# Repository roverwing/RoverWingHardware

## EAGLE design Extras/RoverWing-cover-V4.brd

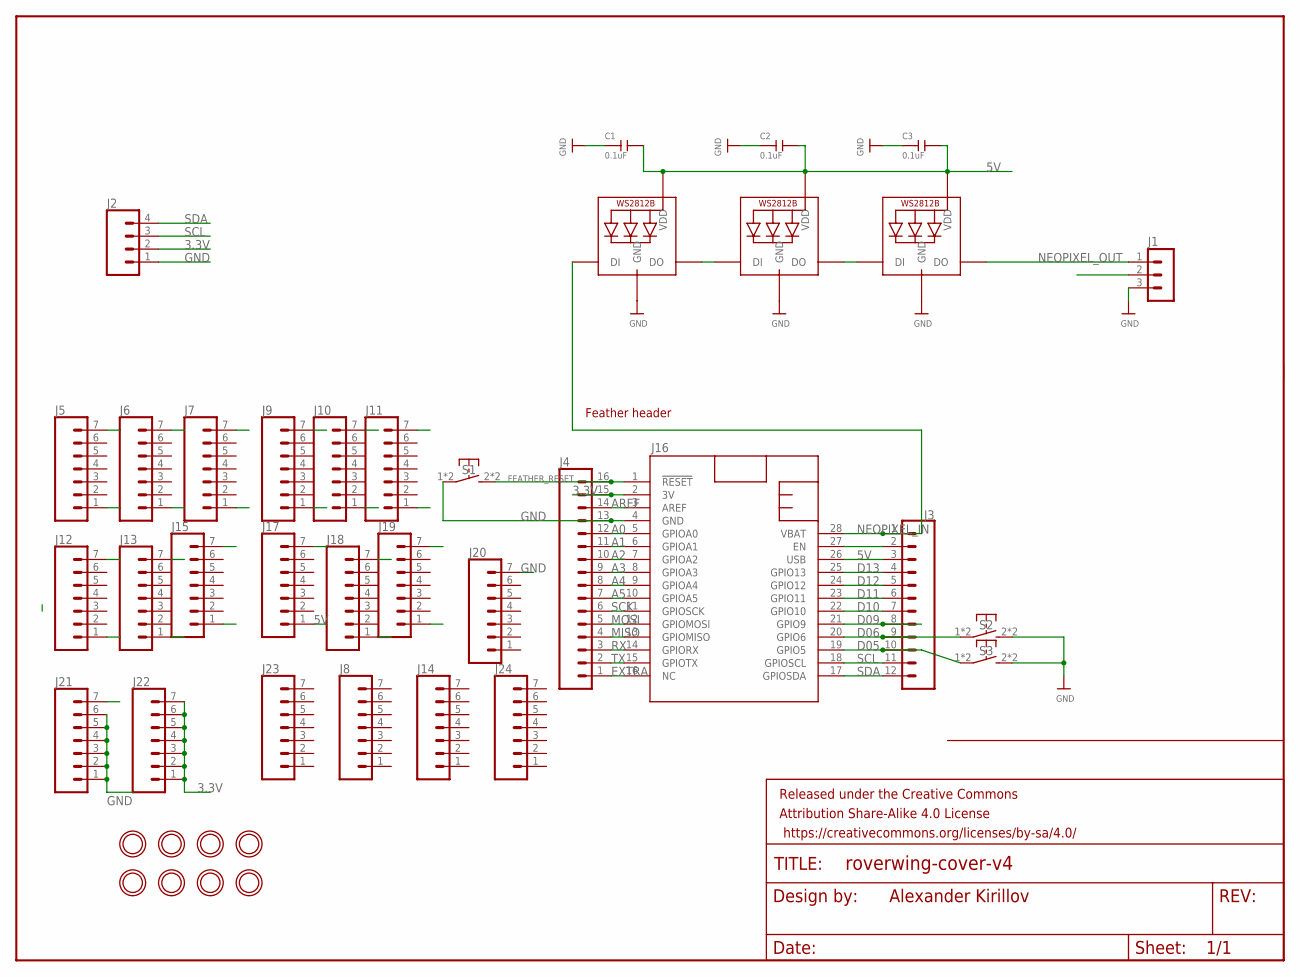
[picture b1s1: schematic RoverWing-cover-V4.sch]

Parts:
C1, C2, C3: 0.1uF; C0805
FRAME2: FRAME-LETTERNO_PACKAGE; DUMMY
J1: HEADER-PH-3P; B3B-PH-K
J2: CONN_04; 1X04
J3: CONN_12NO_SILK; 1X12_NO_SILK
J4: CONN_161X16_NO_SILK; 1X16_NO_SILK
J5, J6, J7, J8, J9, J10, J11, J12, J13, J14, J15, J17, J18, J19, J20, J21, J22, J23, J24: CONN_07NO_SILK; 1X07_NO_SILK
J16: FEATHERWING_NODIM; FEATHERWING_DIM
LED1, LED2, LED3: WS2812B5050; WS2812B
S1, S2, S3: SW-TACTILE-4.5X4.5_SMD; TL3305
U$3, U$4, U$14, U$15, U$24, U$25, U$26, U$27: MOUNTINGHOLE3.0_NPH; MOUNTINGHOLE_3.0_NPH

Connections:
3.3V: J2.2, J4.15, J16.2 (3V), J22.1, J22.2, J22.3, J22.4, J22.5, J22.6, J22.7
5V: C1.2, C2.2, C3.2, J1.2, J3.3, J16.26 (USB), J17.1, LED1.1-VDD (VDD), LED2.1-VDD (VDD), LED3.1-VDD (VDD)
A0: J4.12, J16.5 (GPIOA0), J19.7
A1: J4.11, J16.6 (GPIOA1), J18.7
A2: J4.10, J16.7 (GPIOA2), J17.7
A3: J4.9, J15.7, J16.8 (GPIOA3)
A4: J4.8, J13.7, J16.9 (GPIOA4)
A5: J4.7, J12.7, J16.10 (GPIOA5)
AREF: J4.14, J16.3 (AREF), J21.7
D05: J3.10, J7.1, J16.19 (GPIO5), S3.1, S3.4 (P1)
D06: J3.9, J9.1, J16.20 (GPIO6), S2.1, S2.4 (P1)
D09: J3.8, J10.1, J16.21 (GPIO9)
D10: J3.7, J11.1, J16.22 (GPIO10)
D11: J3.6, J12.1, J16.23 (GPIO11)
D12: J3.5, J13.1, J16.24 (GPIO12)
D13: J3.4, J15.1, J16.25 (GPIO13)
EXTRA: J4.1, J5.7, J16.16 (NC)
FEATHER_RESET: J4.16, J16.1 (!RESET), S1.2 (S1), S1.3 (S1)
GND: C1.1, C2.1, C3.1, J1.3, J2.1, J4.13, J16.4 (GND), J20.7, J21.1, J21.2, J21.3, J21.4, J21.5, J21.6, LED1.3-GND (GND), LED2.3-GND (GND), LED3.3-GND (GND), S1.1, S1.4 (P1), S2.2 (S1), S2.3 (S1), S3.2 (S1), S3.3 (S1)
MISO: J4.4, J9.7, J16.13 (GPIOMISO)
MOSI: J4.5, J10.7, J16.12 (GPIOMOSI)
unnamed: LED2.2-DOUT (DO), LED3.4-DIN (DI)
unnamed: LED1.2-DOUT (DO), LED2.4-DIN (DI)
unnamed: J3.2, J16.27 (EN), J18.1
NEOPIXEL_IN: J3.1, J16.28 (VBAT), LED1.4-DIN (DI)
NEOPIXEL_OUT: J1.1, LED3.2-DOUT (DO)
RX: J4.3, J7.7, J16.14 (GPIORX)
SCK: J4.6, J11.7, J16.11 (GPIOSCK)
SCL: J2.3, J3.11, J6.1, J16.18 (GPIOSCL)
SDA: J2.4, J3.12, J5.1, J16.17 (GPIOSDA)
TX: J4.2, J6.7, J16.15 (GPIOTX)

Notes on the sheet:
Alexander Kirillov
Feather header

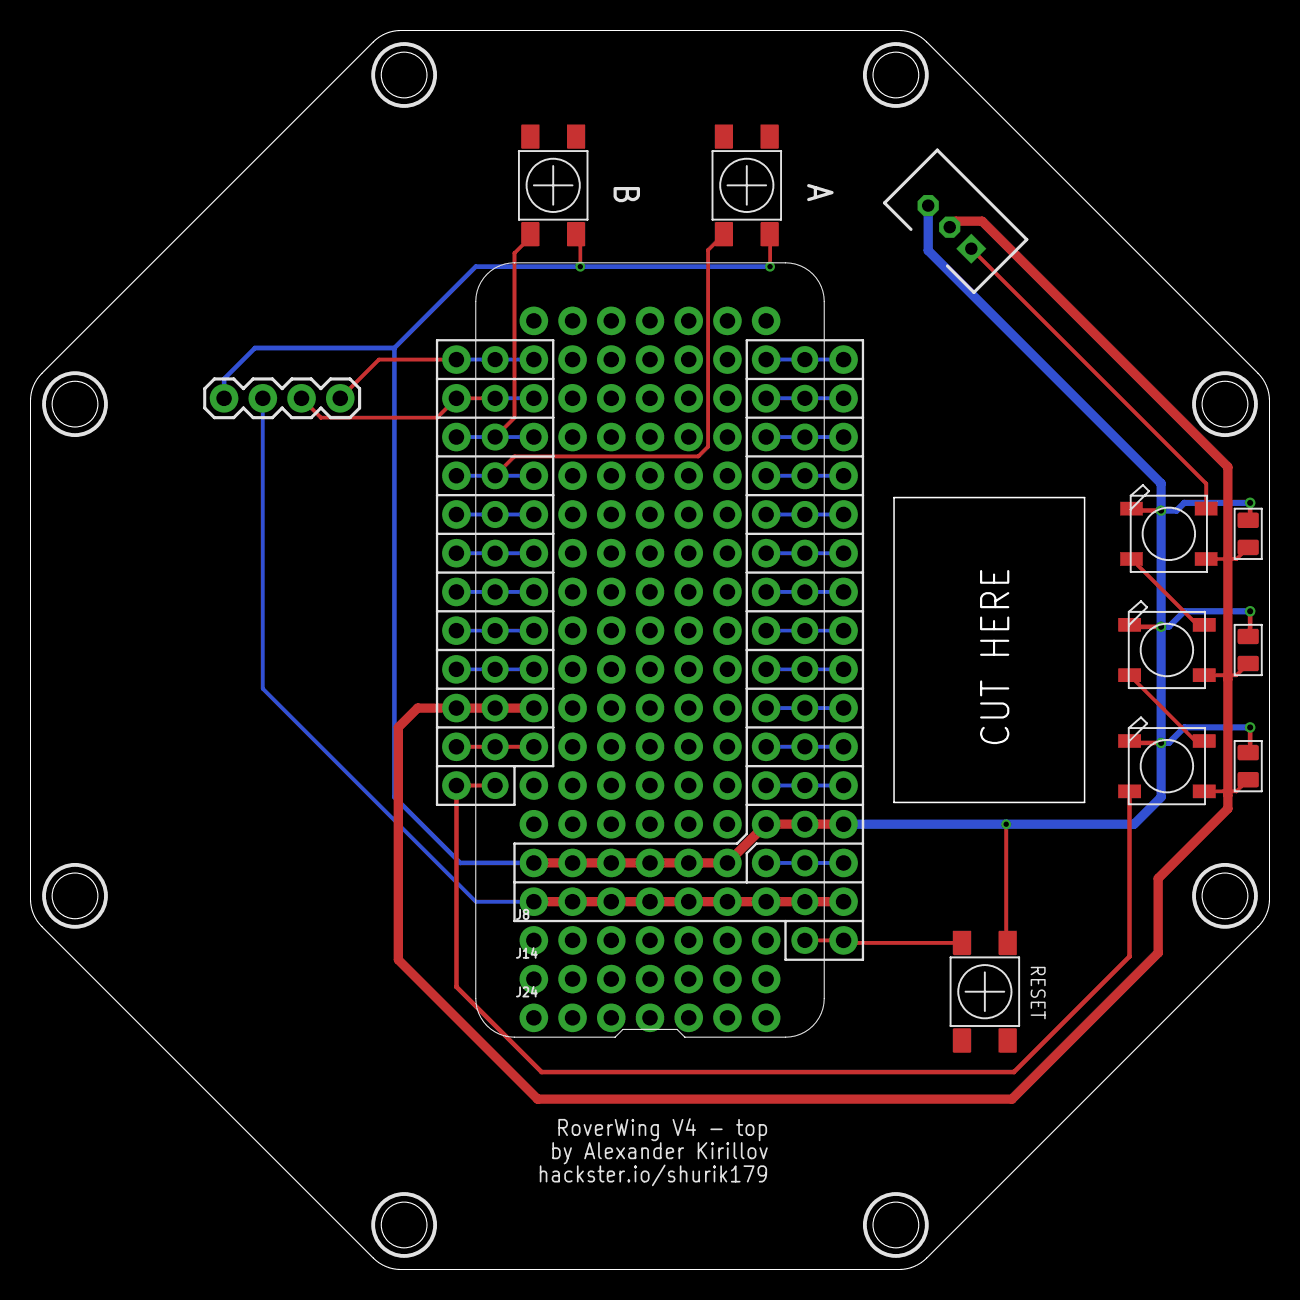
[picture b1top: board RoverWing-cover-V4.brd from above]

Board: 2 copper layers, 81.3 x 81.3 mm, 42 parts (0 on the bottom side), 31 nets.

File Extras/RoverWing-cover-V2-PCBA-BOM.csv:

Order list for /Users/davidbershadsky/Documents/Roverwing/RoverWingHardware/Extras/RoverWing-cover-V2.0.sch
Exported from EAGLE with DesignLink

Quantity	Value	Package	Order code	Manufacturer	Manuf. Code	Availability	Price (from)	Description
3	0.1uF	C0805	96Y8186	AVX	04025C104KAT2A	9540	0.131	AVX - 04025C104KAT2A - SMD Multilayer Ceramic Capacitor, 0.1 &#181;F, 50 V, 0402 [1005 Metric], &#177; 10%, X7R
1	FRAME-LETTERNO_PACKAGE	DUMMY	unknown					
1	HEADER-PH-3PSIDEENTRY	S3B-PH-K	38K8070	JST (JAPAN SOLDERLESS TERMINALS)	S3B-PH-K-S (LF)(SN)	7505	0.075	JST (JAPAN SOLDERLESS TERMINALS) - S3B-PH-K-S (LF)(SN) - Pin Header, Wire-to-Board, 2 mm, 1 Rows, 3 Contacts, Through Hole, PH Series
1		1X04	unknown					
1		1X12_NO_SILK	unknown					
1		1X16_NO_SILK	unknown					
4	HEADER-PH-6PSIDEENTRY	S6B-PH-K	unknown					
8		1X06_NO_SILK	unknown					
1	FEATHERWING_NODIM	FEATHERWING_DIM	unknown					
17		1X07_NO_SILK	unknown					
3		LED3535	77Y5297	ADAFRUIT	2659	0	49.5	ADAFRUIT - 2659 - NEOPIXEL MINI 3535 RGB LEDS W/ INTEGRATED DRIVER CHIP - WHITE - PACK OF 10
3	SW-TACTILE-4.5X4.5_SMD	TL3305	84Y2774	E-SWITCH	TL3305AF160QG	2716	0.126	E-SWITCH - TL3305AF160QG - Tactile Switch, Ultraminiature, TL3305 Series, Top Actuated, Surface Mount, Round Button, 160 gf
8	MOUNTINGHOLE3.0_NPH	MOUNTINGHOLE_3.0_NPH	unknown

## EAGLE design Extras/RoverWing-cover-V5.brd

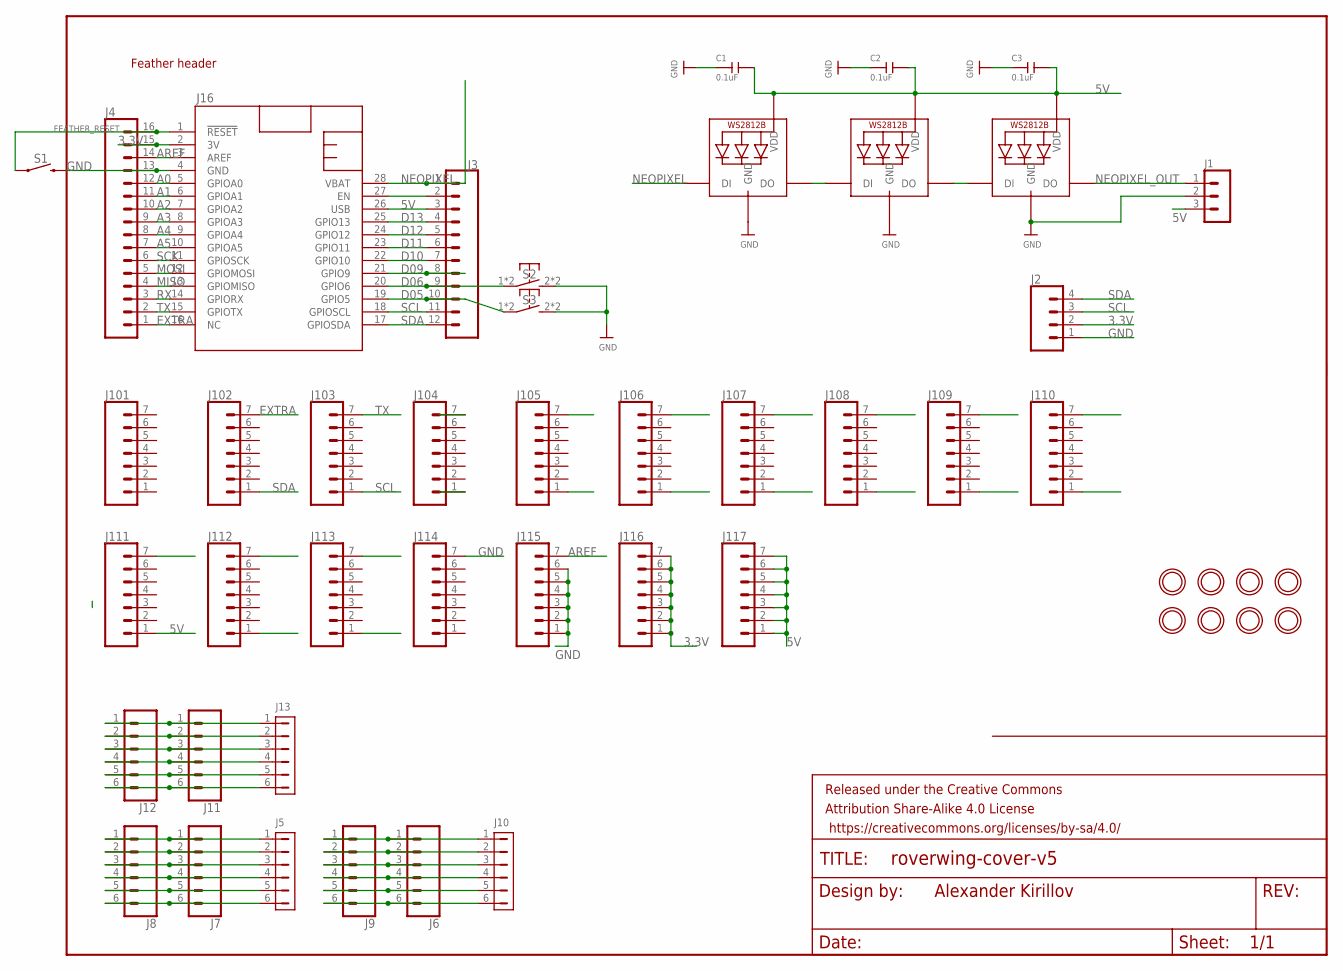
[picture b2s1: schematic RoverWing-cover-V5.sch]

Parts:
C1, C2, C3: 0.1uF; C0805
FRAME2: FRAME-LETTERNO_PACKAGE; DUMMY
J1: HEADER-PH-3PSIDEENTRY; S3B-PH-K
J2: CONN_04; 1X04
J3: CONN_12NO_SILK; 1X12_NO_SILK
J4: CONN_161X16_NO_SILK; 1X16_NO_SILK
J5, J10, J13: HEADER-PH-6PSIDEENTRY; S6B-PH-K
J6, J7, J8, J9, J11, J12: CONN_06NO_SILK_NO_POP; 1X06_NO_SILK
J16: FEATHERWING_NODIM; FEATHERWING_DIM
J101, J102, J103, J104, J105, J106, J107, J108, J109, J110, J111, J112, J113, J114, J115, J116, J117: CONN_07NO_SILK; 1X07_NO_SILK
LED1, LED2, LED3: WS2812B5050; WS2812B
S1: MOMENTARY-SWITCH-SPST-PTH-6.0MM; TACTILE_SWITCH_PTH_6.0MM
S2, S3: SW-TACTILE-4.5X4.5_SMD; TL3305
U$3, U$4, U$14, U$15, U$24, U$25, U$26, U$27: MOUNTINGHOLE3.0_NPH; MOUNTINGHOLE_3.0_NPH

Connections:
3.3V: J2.2, J4.15, J16.2 (3V), J116.1, J116.2, J116.3, J116.4, J116.5, J116.6, J116.7
5V: C1.2, C2.2, C3.2, J1.3, J3.3, J16.26 (USB), J111.1, J117.1, J117.2, J117.3, J117.4, J117.5, J117.6, J117.7, LED1.1-VDD (VDD), LED2.1-VDD (VDD), LED3.1-VDD (VDD)
A0: J4.12, J16.5 (GPIOA0), J113.7
A1: J4.11, J16.6 (GPIOA1), J112.7
A2: J4.10, J16.7 (GPIOA2), J111.7
A3: J4.9, J16.8 (GPIOA3), J110.7
A4: J4.8, J16.9 (GPIOA4), J109.7
A5: J4.7, J16.10 (GPIOA5), J108.7
AREF: J4.14, J16.3 (AREF), J115.7
D05: J3.10, J16.19 (GPIO5), J104.1, S3.1, S3.4 (P1)
D06: J3.9, J16.20 (GPIO6), J105.1, S2.1, S2.4 (P1)
D09: J3.8, J16.21 (GPIO9), J106.1
D10: J3.7, J16.22 (GPIO10), J107.1
D11: J3.6, J16.23 (GPIO11), J108.1
D12: J3.5, J16.24 (GPIO12), J109.1
D13: J3.4, J16.25 (GPIO13), J110.1
EXTRA: J4.1, J16.16 (NC), J102.7
FEATHER_RESET: J4.16, J16.1 (!RESET), S1.1
GND: C1.1, C2.1, C3.1, J1.2, J2.1, J4.13, J16.4 (GND), J114.7, J115.1, J115.2, J115.3, J115.4, J115.5, J115.6, LED1.3-GND (GND), LED2.3-GND (GND), LED3.3-GND (GND), S1.3 (2), S2.2 (S1), S2.3 (S1), S3.2 (S1), S3.3 (S1)
MISO: J4.4, J16.13 (GPIOMISO), J105.7
MOSI: J4.5, J16.12 (GPIOMOSI), J106.7
unnamed: LED2.2-DOUT (DO), LED3.4-DIN (DI)
unnamed: J5.1, J7.1, J8.1
unnamed: LED1.2-DOUT (DO), LED2.4-DIN (DI)
unnamed: J5.2, J7.2, J8.2
unnamed: J5.3, J7.3, J8.3
unnamed: J5.4, J7.4, J8.4
unnamed: J5.5, J7.5, J8.5
unnamed: J5.6, J7.6, J8.6
unnamed: J6.1, J9.1, J10.1
unnamed: J6.2, J9.2, J10.2
unnamed: J6.3, J9.3, J10.3
unnamed: J6.4, J9.4, J10.4
unnamed: J6.5, J9.5, J10.5
unnamed: J6.6, J9.6, J10.6
unnamed: J11.1, J12.1, J13.1
unnamed: J11.2, J12.2, J13.2
unnamed: J11.3, J12.3, J13.3
unnamed: J11.4, J12.4, J13.4
unnamed: J11.5, J12.5, J13.5
unnamed: J11.6, J12.6, J13.6
unnamed: J3.2, J16.27 (EN), J112.1
NEOPIXEL: J3.1, J16.28 (VBAT), LED1.4-DIN (DI)
NEOPIXEL_OUT: J1.1, LED3.2-DOUT (DO)
RX: J4.3, J16.14 (GPIORX), J104.7
SCK: J4.6, J16.11 (GPIOSCK), J107.7
SCL: J2.3, J3.11, J16.18 (GPIOSCL), J103.1
SDA: J2.4, J3.12, J16.17 (GPIOSDA), J102.1
TX: J4.2, J16.15 (GPIOTX), J103.7

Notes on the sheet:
Alexander Kirillov
Feather header

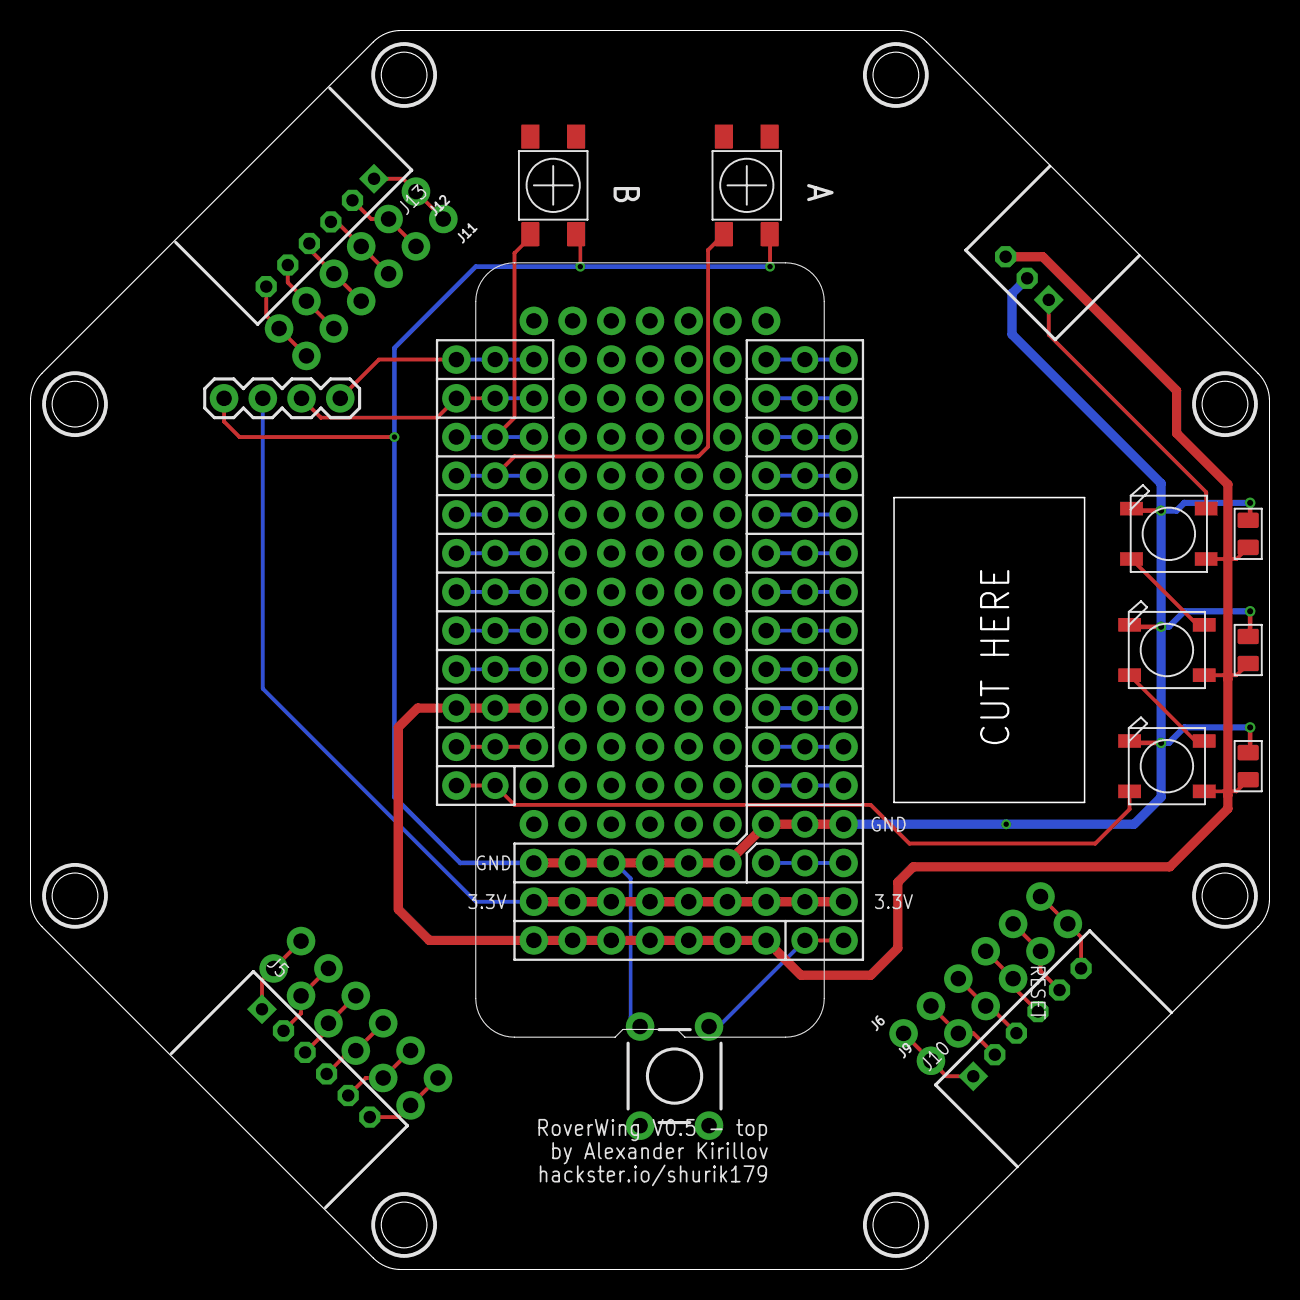
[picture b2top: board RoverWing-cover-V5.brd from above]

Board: 2 copper layers, 81.3 x 81.3 mm, 49 parts (0 on the bottom side), 49 nets.

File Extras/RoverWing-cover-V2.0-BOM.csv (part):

"Part";"Value";"Device";"Package";"Description";"DESIGNER";"MANUFACTURER";"MF";"MPN";"OC_NEWARK";"PARTNO";"PROD_ID";"VERSION";
"C1";"0.1uF";"CAP-CERAMIC-SMD-0805";"C0805";"";"";"";"AVX";"04025C104KAT2A";"96Y8186";"";"";"";
"C2";"0.1uF";"CAP-CERAMIC-SMD-0805";"C0805";"";"";"";"AVX";"04025C104KAT2A";"96Y8186";"";"";"";
"C3";"0.1uF";"CAP-CERAMIC-SMD-0805";"C0805";"";"";"";"AVX";"04025C104KAT2A";"96Y8186";"";"";"";
"FRAME2";"FRAME-LETTERNO_PACKAGE";"FRAME-LETTERNO_PACKAGE";"DUMMY";"Schematic Frame - Letter";"Nobody";"";"";"";"unknown";"";"";"v01";
"J1";"HEADER-PH-3PSIDEENTRY";"HEADER-PH-3PSIDEENTRY";"S3B-PH-K";"HEADER";"";"";"JST (JAPAN SOLDERLESS TERMINALS)";"S3B-PH-K-S (LF)(SN)";"38K8070";"S3B-PH-K-S(LF)(SN)";"";"";
"J2";"";"CONN_04";"1X04";"Multi connection point. Often used as Generic Header-pin footprint for 0.1 inch spaced/style header connections";"";"";"";"";"unknown";"";"CONN-09696";"";
"J3";"";"CONN_12NO_SILK";"1X12_NO_SILK";"Multi connection point. Often used as Generic Header-pin footprint for 0.1 inch spaced/style header connections";"";"";"";"";"unknown";"";"";"";
"J4";"";"CONN_161X16_NO_SILK";"1X16_NO_SILK";"Multi connection point. Often used as Generic Header-pin footprint for 0.1 inch spaced/style header connections";"";"";"";"";"unknown";"";"";"";
"J5";"HEADER-PH-6PSIDEENTRY";"HEADER-PH-6PSIDEENTRY";"S6B-PH-K";"JST PH header, 6 pos";"";"";"";"";"unknown";"";"";"";
"J6";"";"CONN_06NO_SILK_NO_POP";"1X06_NO_SILK";"Multi connection point. Often used as Generic Header-pin footprint for 0.1 inch spaced/style header connections";"";"";"";"";"unknown";"";"";"";
"J7";"";"CONN_06NO_SILK_NO_POP";"1X06_NO_SILK";"Multi connection point. Often used as Generic Header-pin footprint for 0.1 inch spaced/style header connections";"";"";"";"";"unknown";"";"";"";
"J8";"";"CONN_06NO_SILK_NO_POP";"1X06_NO_SILK";"Multi connection point. Often used as Generic Header-pin footprint for 0.1 inch spaced/style header connections";"";"";"";"";"unknown";"";"";"";
"J9";"";"CONN_06NO_SILK_NO_POP";"1X06_NO_SILK";"Multi connection point. Often used as Generic Header-pin footprint for 0.1 inch spaced/style header connections";"";"";"";"";"unknown";"";"";"";
"J10";"HEADER-PH-6PSIDEENTRY";"HEADER-PH-6PSIDEENTRY";"S6B-PH-K";"JST PH header, 6 pos";"";"";"";"";"unknown";"";"";"";
"J11";"";"CONN_06NO_SILK_NO_POP";"1X06_NO_SILK";"Multi connection point. Often used as Generic Header-pin footprint for 0.1 inch spaced/style header connections";"";"";"";"";"unknown";"";"";"";
"J12";"";"CONN_06NO_SILK_NO_POP";"1X06_NO_SILK";"Multi connection point. Often used as Generic Header-pin footprint for 0.1 inch spaced/style header connections";"";"";"";"";"unknown";"";"";"";
"J13";"HEADER-PH-6PSIDEENTRY";"HEADER-PH-6PSIDEENTRY";"S6B-PH-K";"JST PH header, 6 pos";"";"";"";"";"unknown";"";"";"";
"J14";"";"CONN_06NO_SILK_NO_POP";"1X06_NO_SILK";"Multi connection point. Often used as Generic Header-pin footprint for 0.1 inch spaced/style header connections";"";"";"";"";"unknown";"";"";"";
"J15";"";"CONN_06NO_SILK_NO_POP";"1X06_NO_SILK";"Multi connection point. Often used as Generic Header-pin footprint for 0.1 inch spaced/style header connections";"";"";"";"";"unknown";"";"";"";
"J16";"FEATHERWING_NODIM";"FEATHERWING_NODIM";"FEATHERWING_DIM";"Adafruit Feather";"";"";"";"";"unknown";"";"";"";
"J17";"HEADER-PH-6PSIDEENTRY";"HEADER-PH-6PSIDEENTRY";"S6B-PH-K";"JST PH header, 6 pos";"";"";"";"";"unknown";"";"";"";
"J101";"";"CONN_07NO_SILK";"1X07_NO_SILK";"Multi connection point. Often used as Generic Header-pin footprint for 0.1 inch spaced/style header connections";"";"";"";"";"unknown";"";"";"";
"J102";"";"CONN_07NO_SILK";"1X07_NO_SILK";"Multi connection point. Often used as Generic Header-pin footprint for 0.1 inch spaced/style header connections";"";"";"";"";"unknown";"";"";"";
"J103";"";"CONN_07NO_SILK";"1X07_NO_SILK";"Multi connection point. Often used as Generic Header-pin footprint for 0.1 inch spaced/style header connections";"";"";"";"";"unknown";"";"";"";
"J104";"";"CONN_07NO_SILK";"1X07_NO_SILK";"Multi connection point. Often used as Generic Header-pin footprint for 0.1 inch spaced/style header connections";"";"";"";"";"unknown";"";"";"";
"J105";"";"CONN_07NO_SILK";"1X07_NO_SILK";"Multi connection point. Often used as Generic Header-pin footprint for 0.1 inch spaced/style header connections";"";"";"";"";"unknown";"";"";"";
"J106";"";"CONN_07NO_SILK";"1X07_NO_SILK";"Multi connection point. Often used as Generic Header-pin footprint for 0.1 inch spaced/style header connections";"";"";"";"";"unknown";"";"";"";
"J107";"";"CONN_07NO_SILK";"1X07_NO_SILK";"Multi connection point. Often used as Generic Header-pin footprint for 0.1 inch spaced/style header connections";"";"";"";"";"unknown";"";"";"";
"J108";"";"CONN_07NO_SILK";"1X07_NO_SILK";"Multi connection point. Often used as Generic Header-pin footprint for 0.1 inch spaced/style header connections";"";"";"";"";"unknown";"";"";"";
"J109";"";"CONN_07NO_SILK";"1X07_NO_SILK";"Multi connection point. Often used as Generic Header-pin footprint for 0.1 inch spaced/style header connections";"";"";"";"";"unknown";"";"";"";
"J110";"";"CONN_07NO_SILK";"1X07_NO_SILK";"Multi connection point. Often used as Generic Header-pin footprint for 0.1 inch spaced/style header connections";"";"";"";"";"unknown";"";"";"";
"J111";"";"CONN_07NO_SILK";"1X07_NO_SILK";"Multi connection point. Often used as Generic Header-pin footprint for 0.1 inch spaced/style header connections";"";"";"";"";"unknown";"";"";"";
"J112";"";"CONN_07NO_SILK";"1X07_NO_SILK";"Multi connection point. Often used as Generic Header-pin footprint for 0.1 inch spaced/style header connections";"";"";"";"";"unknown";"";"";"";
"J113";"";"CONN_07NO_SILK";"1X07_NO_SILK";"Multi connection point. Often used as Generic Header-pin footprint for 0.1 inch spaced/style header connections";"";"";"";"";"unknown";"";"";"";
"J114";"";"CONN_07NO_SILK";"1X07_NO_SILK";"Multi connection point. Often used as Generic Header-pin footprint for 0.1 inch spaced/style header connections";"";"";"";"";"unknown";"";"";"";
"J115";"";"CONN_07NO_SILK";"1X07_NO_SILK";"Multi connection point. Often used as Generic Header-pin footprint for 0.1 inch spaced/style header connections";"";"";"";"";"unknown";"";"";"";
"J116";"";"CONN_07NO_SILK";"1X07_NO_SILK";"Multi connection point. Often used as Generic Header-pin footprint for 0.1 inch spaced/style header connections";"";"";"";"";"unknown";"";"";"";
"J117";"";"CONN_07NO_SILK";"1X07_NO_SILK";"Multi connection point. Often used as Generic Header-pin footprint for 0.1 inch spaced/style header connections";"";"";"";"";"unknown";"";"";"";
"LED1";"";"WS2812B3535";"LED3535";"";"";"Worldsemi";"ADAFRUIT";"2659";"77Y5297";"WS2812B-3535 ";"";"";
"LED2";"";"WS2812B3535";"LED3535";"";"";"Worldsemi";"ADAFRUIT";"2659";"77Y5297";"WS2812B-3535 ";"";"";
"LED3";"";"WS2812B3535";"LED3535";"";"";"Worldsemi";"ADAFRUIT";"2659";"77Y5297";"WS2812B-3535 ";"";"";
"S1";"SW-TACTILE-4.5X4.5_SMD";"SW-TACTILE-4.5X4.5_SMD";"TL3305";"Tactile Switche";"";"";"E-SWITCH";"TL3305AF160QG";"84Y2774";"";"";"";
"S2";"SW-TACTILE-4.5X4.5_SMD";"SW-TACTILE-4.5X4.5_SMD";"TL3305";"Tactile Switche";"";"";"E-SWITCH";"TL3305AF160QG";"84Y2774";"";"";"";
"S3";"SW-TACTILE-4.5X4.5_SMD";"SW-TACTILE-4.5X4.5_SMD";"TL3305";"Tactile Switche";"";"";"E-SWITCH";"TL3305AF160QG";"84Y2774";"";"";"";
"U$3";"MOUNTINGHOLE3.0_NPH";"MOUNTINGHOLE3.0_NPH";"MOUNTINGHOLE_3.0_NPH";"Mounting Hole";"";"";"";"";"unknown";"";"";"";
"U$4";"MOUNTINGHOLE3.0_NPH";"MOUNTINGHOLE3.0_NPH";"MOUNTINGHOLE_3.0_NPH";"Mounting Hole";"";"";"";"";"unknown";"";"";"";
"U$14";"MOUNTINGHOLE3.0_NPH";"MOUNTINGHOLE3.0_NPH";"MOUNTINGHOLE_3.0_NPH";"Mounting Hole";"";"";"";"";"unknown";"";"";"";
"U$15";"MOUNTINGHOLE3.0_NPH";"MOUNTINGHOLE3.0_NPH";"MOUNTINGHOLE_3.0_NPH";"Mounting Hole";"";"";"";"";"unknown";"";"";"";
"U$24";"MOUNTINGHOLE3.0_NPH";"MOUNTINGHOLE3.0_NPH";"MOUNTINGHOLE_3.0_NPH";"Mounting Hole";"";"";"";"";"unknown";"";"";"";
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
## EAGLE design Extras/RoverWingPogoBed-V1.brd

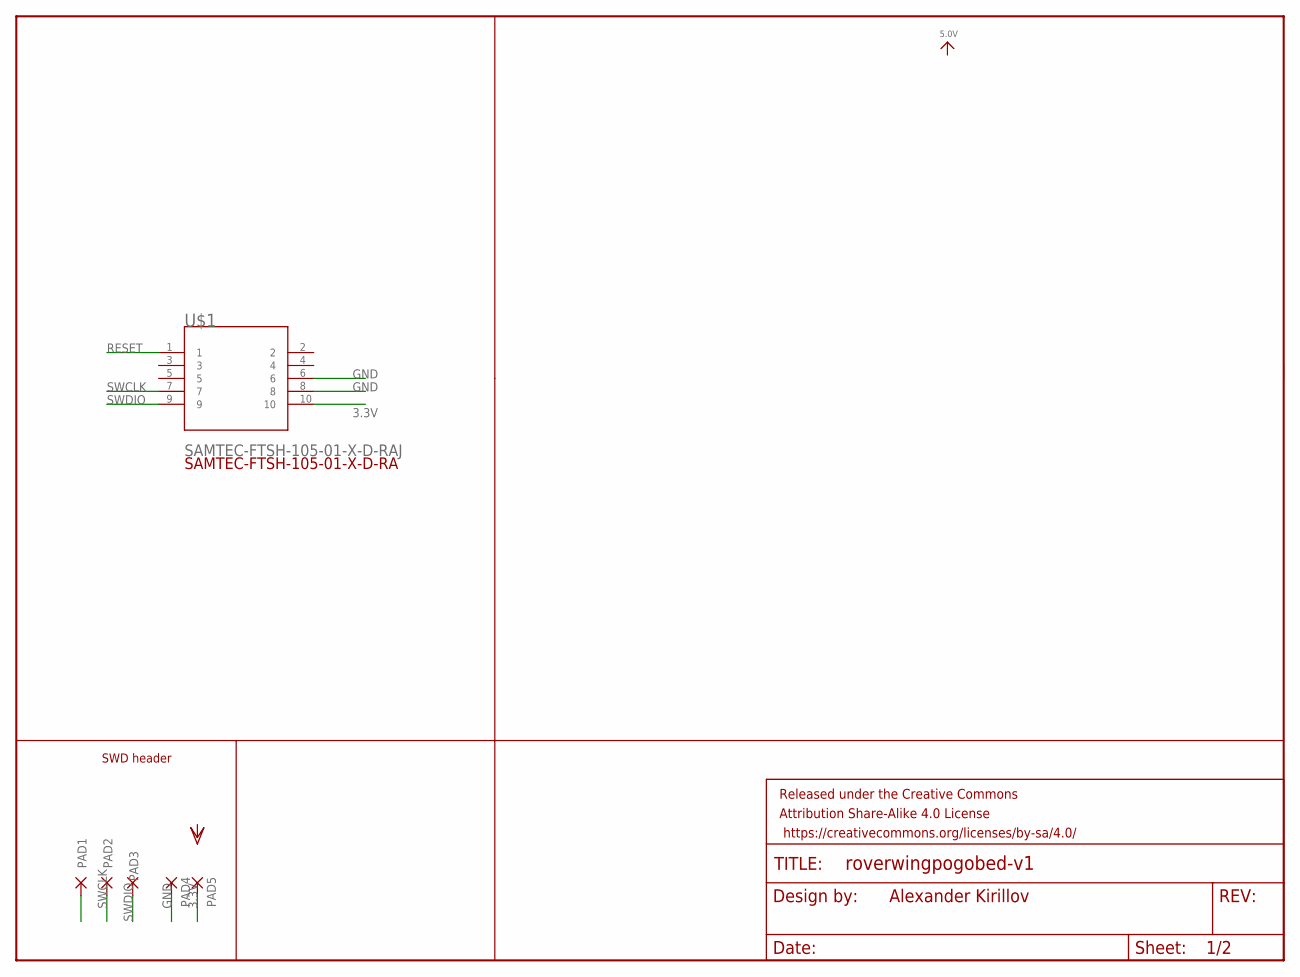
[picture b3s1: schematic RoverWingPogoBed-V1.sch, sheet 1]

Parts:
FRAME2: FRAME-LETTERNO_PACKAGE; DUMMY
PAD1, PAD2, PAD3, PAD4, PAD5: 2,15/1,0
U$1: SAMTEC-FTSH-105-01-X-D-RAJ; SAMTEC-FTSH-105-01-X-D-RA

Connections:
3.3V: PAD5.1, U$1.10
GND: PAD4.1, U$1.6, U$1.8
RESET: PAD1.1, U$1.1
SWCLK: PAD2.1, U$1.7
SWDIO: PAD3.1, U$1.9

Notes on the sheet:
SWD header
Alexander Kirillov

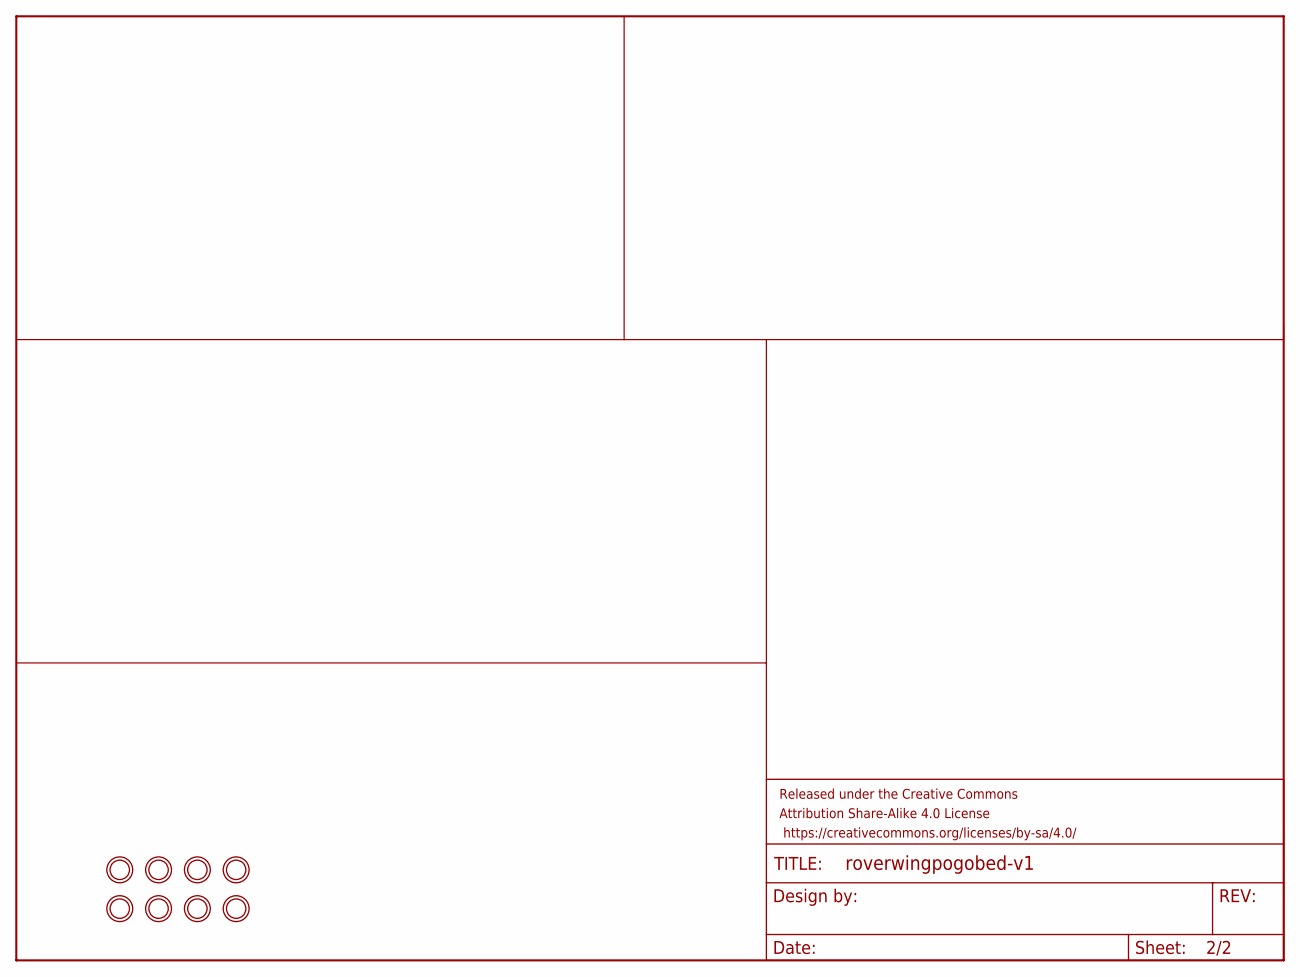
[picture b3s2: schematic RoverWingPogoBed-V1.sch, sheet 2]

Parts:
FRAME1: FRAME-LETTERNO_PACKAGE; DUMMY
U$3, U$4, U$14, U$15, U$24, U$25, U$26, U$27: MOUNTINGHOLE3.0_NPH; MOUNTINGHOLE_3.0_NPH

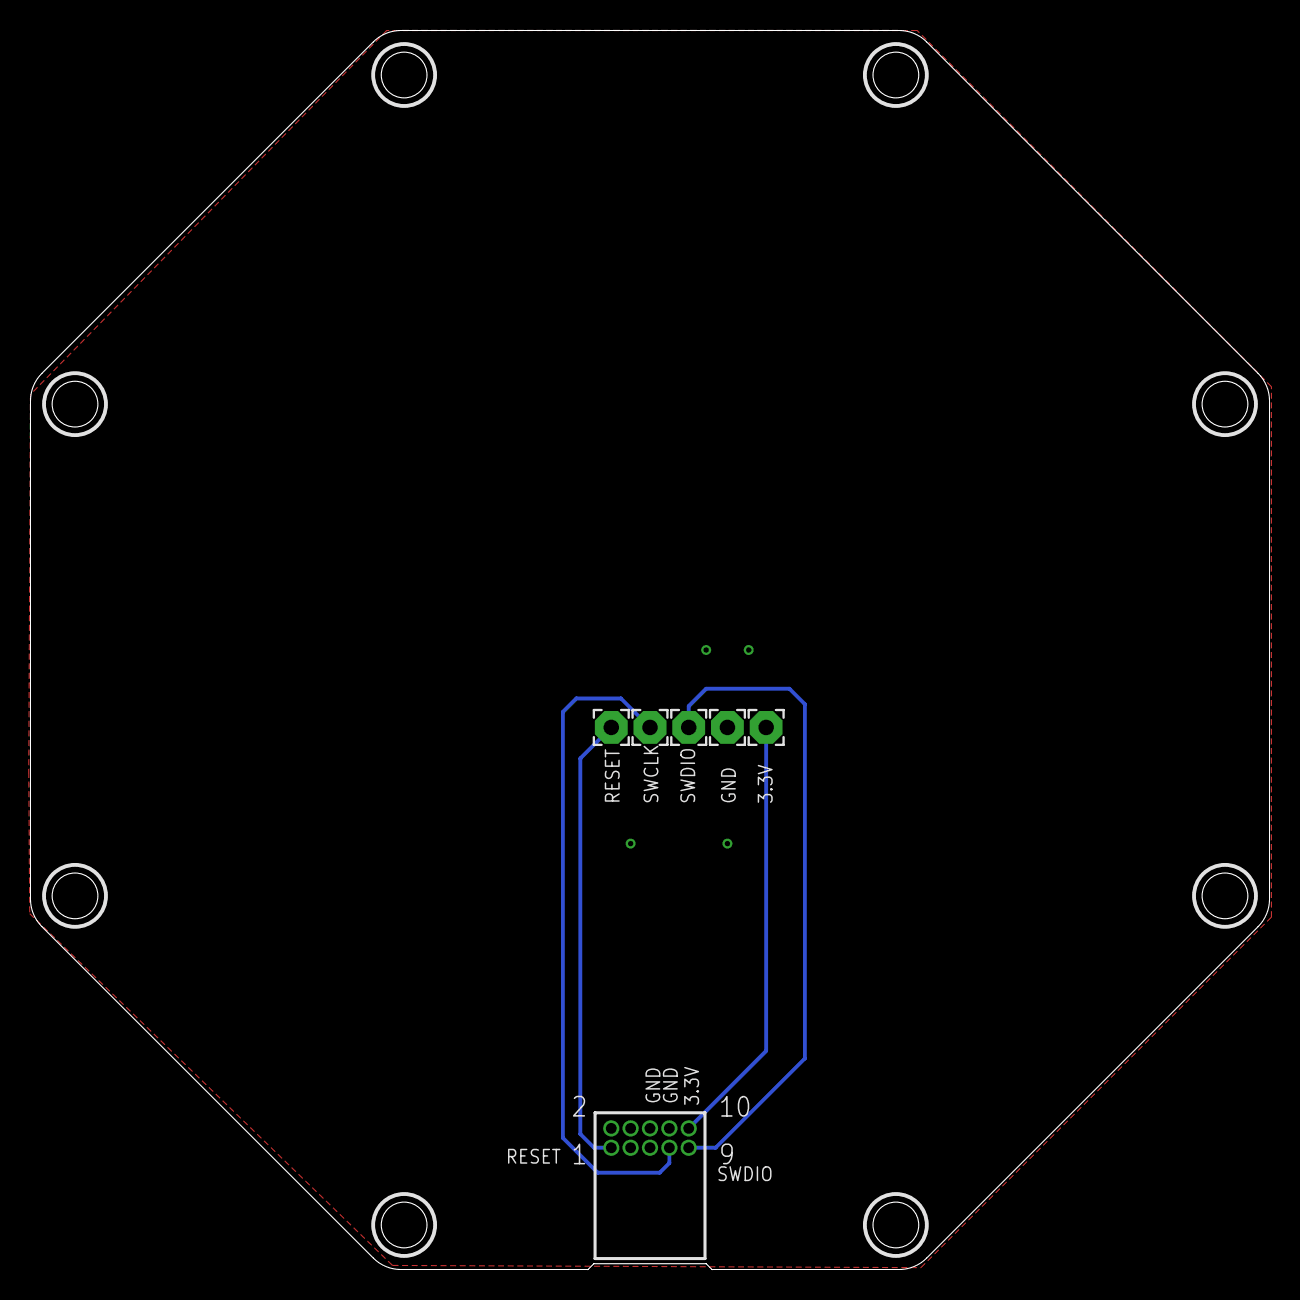
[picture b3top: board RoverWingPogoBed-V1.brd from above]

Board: 2 copper layers, 81.3 x 81.3 mm, 16 parts (0 on the bottom side), 5 nets.

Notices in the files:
parts and their libraries:
SparkFun-Aesthetics: Licensing: Creative Commons ShareAlike 4.0 International - https://creativecommons.org/licenses/by-sa/4.0
SparkFun-Aesthetics: Released under the Creative Commons Attribution Share-Alike 4.0 License
SparkFun-Aesthetics: https://creativecommons.org/licenses/by-sa/4.0
